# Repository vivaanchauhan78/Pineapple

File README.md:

# Pineapple
A not-so-small 60% keyboard that I made!

I have a mouse on my other setup up but I didn't have a keyboard, so I thought of making one!

| Item         | Cost    | Link |
|--------------|---------|------|
| Rpp2040      | $3.46   | [Buy on aliexpress](https://www.aliexpress.us/item/3256806217238860.html?spm=a2g0o.cart.0.0.2d6c38daTqjGkV&mp=1&pdp_npi=5%40dis%21USD%21USD%203.46%21USD%200.99%21%21USD%200.99%21%21%21%402103205217531554636108924eb90a%2112000037042067691%21ct%21US%216426456965%21%211%210&pdp_ext_f=%7B%22cart2PdpParams%22%3A%7B%22pdpBusinessMode%22%3A%22retail%22%7D%7D&_gl=1*w7bknt*_gcl_au*MTQ2NDQ1NzgyLjE3NTI4NzgwODk.*_ga*MTk1MzE5NzUxMi4xNzUzMDQ5NjA5*_ga_VED1YSGNC7*czE3NTMxNTQ2MDQkbzQkZzEkdDE3NTMxNTU0NjMkajMzJGwwJGgw&gatewayAdapt=glo2usa) |
| Switches     | $19.65  | [Buy on AliExpress](https://www.aliexpress.us/item/3256804049630074.html) |
| PCB          | $30.44  | [Buy on Pcbway](https://member.pcbway.com/Order/OrderGroupConfirm/)
| Stabilizers  | $4.11   | [Buy on aliexpress](https://www.aliexpress.us/item/3256807348740208.html?spm=a2g0o.productlist.main.4.7c5d4a6eayveZj&aem_p4p_detail=20250721204006133116881527110000082721&algo_pvid=e2a4ce2c-4b11-4272-be36-e702e015e351&algo_exp_id=e2a4ce2c-4b11-4272-be36-e702e015e351-3&pdp_ext_f=%7B%22order%22%3A%22365%22%2C%22eval%22%3A%221%22%7D&pdp_npi=4%40dis%21USD%214.11%210.99%21%21%2129.35%217.10%21%402103241117531556059128212efb0c%2112000041195815297%21sea%21US%216426456965%21ABX&curPageLogUid=ajEZrvKqLNbd&utparam-url=scene%3Asearch%7Cquery_from%3A&search_p4p_id=20250721204006133116881527110000082721_1) |
| Fasteners    | $14.00  | [Buy on eBay](https://pay.ebay.com/rgxo?action=view&sessionid=1716123654) |
| Diodes       | $1.64   | [Buy on AliExpress](https://www.aliexpress.us/p/trade/confirm.html?availableProductShopcartIds=81023549395923) |
| Keycaps      | $26.51  | [Buy on Amazon](https://www.amazon.com/JSJT-Keycaps-Keycaps-Non-Backlit-Mechanical-Multi-Color/dp/B0BCFCQG2Z/ref=asc_df_B0BCFCQG2Z?tag=bingshoppinga-20&linkCode=df0&hvadid=80333258220081&hvnetw=o&hvqmt=e&hvbmt=be&hvdev=c&hvlocint=&hvlocphy=77507&hvtargid=pla-4583932723308317&msclkid=375f23a88c8a1849a15e4bd658e5279e&th=1) |
| Case         | $4.74   |
| **Total**    | **104.55** | 

Pictures:

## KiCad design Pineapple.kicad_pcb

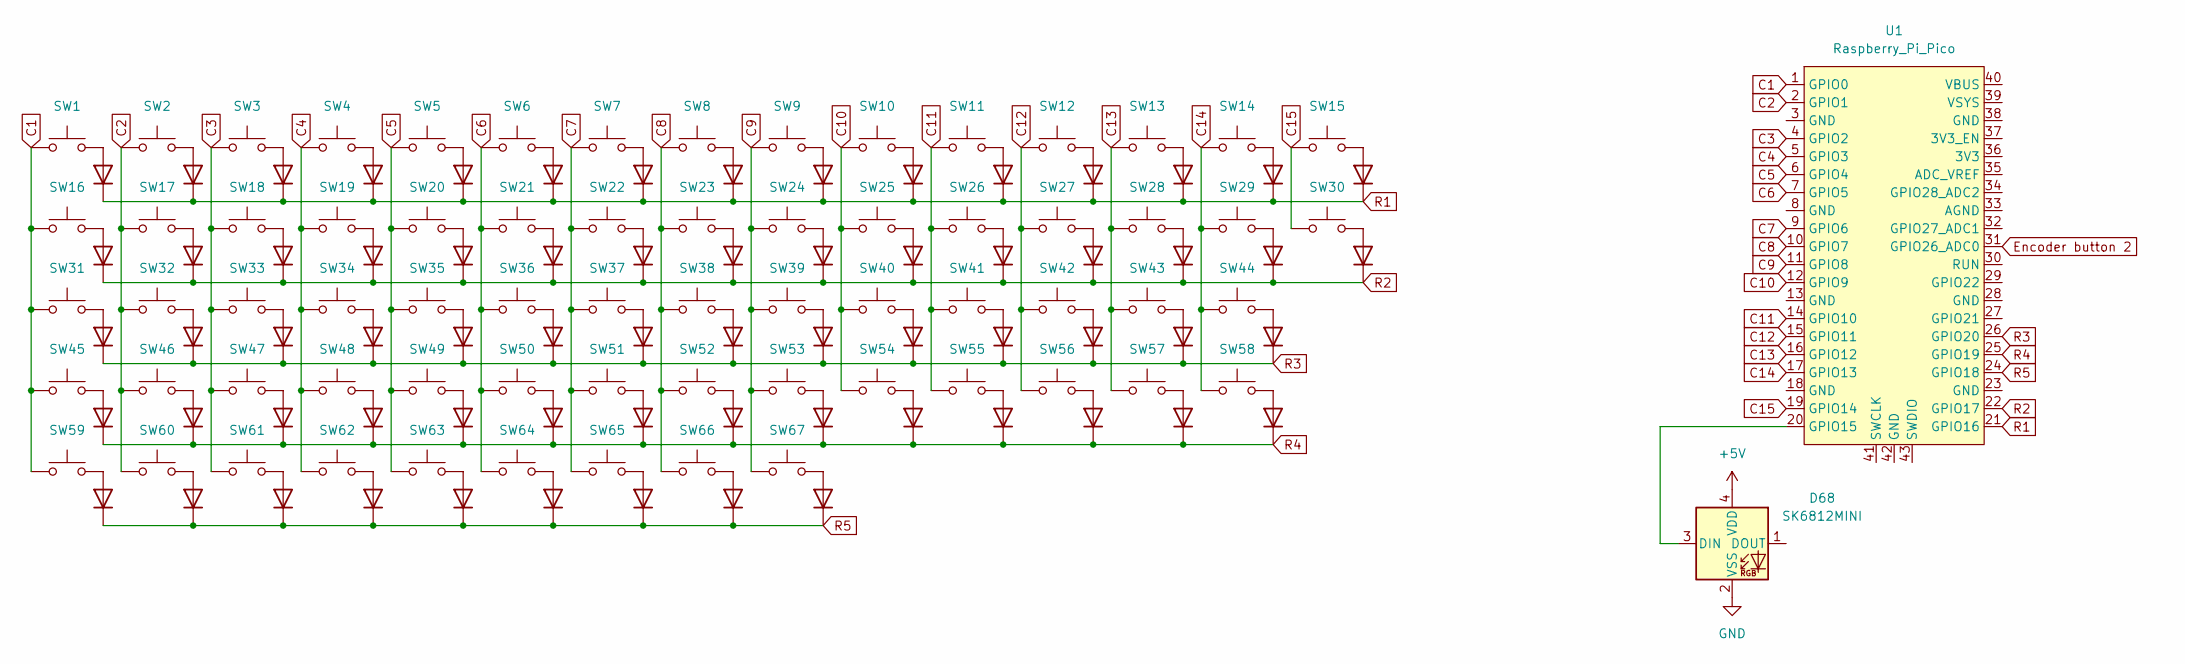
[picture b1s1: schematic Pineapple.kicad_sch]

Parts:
D1, D2, D3, D4, D5, D6, D7, D8, D9, D10, D11, D12, D13, D14, D15, D16, D17, D18, D19, D20, D21, D22, D23, D24, D25, D26, D27, D28, D29, D30, D31, D32, D33, D34, D35, D36, D37, D38, D39, D40, D41, D42, D43, D44, D45, D46, D47, D48, D49, D50, D51, D52, D53, D54, D55, D56, D57, D58, D59, D60, D61, D62, D63, D64, D65, D66, D67: D; D_DO-35_SOD27_P7.62mm_Horizontal
D68: SK6812MINI; LED_SK6812MINI_PLCC4_3.5x3.5mm_P1.75mm
SW1, SW2, SW3, SW4, SW5, SW6, SW7, SW8, SW9, SW10, SW11, SW12, SW13, SW15, SW17, SW18, SW19, SW20, SW21, SW22, SW23, SW24, SW25, SW26, SW27, SW28, SW30, SW32, SW33, SW34, SW35, SW36, SW37, SW38, SW39, SW40, SW41, SW42, SW44, SW46, SW47, SW48, SW49, SW50, SW51, SW52, SW53, SW54, SW55, SW57, SW58, SW65, SW66, SW67: SW_Push; SW_Cherry_MX_1.00u_PCB
SW14, SW31, SW56: SW_Push; SW_Cherry_MX_1.75u_PCB
SW16: SW_Push; SW_Cherry_MX_1.50u_PCB
SW29, SW59, SW60, SW61, SW63, SW64: SW_Push; SW_Cherry_MX_1.25u_PCB
SW43, SW45: SW_Push; SW_Cherry_MX_2.00u_PCB
SW62: SW_Push; SW_Cherry_MX_6.25u_PCB
U1: Raspberry_Pi_Pico

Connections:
+5V: D68.4 (VDD)
C1: SW1.1, SW16.1, SW31.1, SW45.1, SW59.1, U1.1 (GPIO0)
C2: SW2.1, SW17.1, SW32.1, SW46.1, SW60.1, U1.2 (GPIO1)
C3: SW3.2, SW18.1, SW33.1, SW47.1, SW61.1, U1.4 (GPIO2)
C4: SW4.1, SW19.1, SW34.1, SW48.1, SW62.1, U1.5 (GPIO3)
C5: SW5.1, SW20.1, SW35.1, SW49.1, SW63.1, U1.6 (GPIO4)
C6: SW6.1, SW21.1, SW36.1, SW50.1, SW64.1, U1.7 (GPIO5)
C7: SW7.1, SW22.1, SW37.1, SW51.1, SW65.1, U1.9 (GPIO6)
C8: SW8.1, SW23.1, SW38.1, SW52.1, SW66.1, U1.10 (GPIO7)
C9: SW9.1, SW24.1, SW39.1, SW53.1, SW67.1, U1.11 (GPIO8)
C10: SW10.1, SW25.1, SW40.1, SW54.1, U1.12 (GPIO9)
C11: SW11.1, SW26.1, SW41.1, SW55.1, U1.14 (GPIO10)
C12: SW12.1, SW27.1, SW42.1, SW56.1, U1.15 (GPIO11)
C13: SW13.1, SW28.1, SW43.1, SW57.1, U1.16 (GPIO12)
C14: SW14.1, SW29.1, SW44.1, SW58.1, U1.17 (GPIO13)
C15: SW15.1, SW30.1, U1.19 (GPIO14)
Encoder button 1: U1.29 (GPIO22)
Encoder button 2: U1.31 (GPIO26_ADC0)
GND: D68.2 (VSS)
unnamed: D1.2 (A), SW1.2
unnamed: D2.2 (A), SW2.2
unnamed: D3.2 (A), SW3.1
unnamed: D4.2 (A), SW4.2
unnamed: D5.2 (A), SW5.2
unnamed: D6.2 (A), SW6.2
unnamed: D7.2 (A), SW7.2
unnamed: D8.2 (A), SW8.2
unnamed: D9.2 (A), SW9.2
unnamed: D10.2 (A), SW10.2
unnamed: D11.2 (A), SW11.2
unnamed: D12.2 (A), SW12.2
unnamed: D13.2 (A), SW13.2
unnamed: D14.2 (A), SW14.2
unnamed: D15.2 (A), SW15.2
unnamed: D16.2 (A), SW16.2
unnamed: D17.2 (A), SW17.2
unnamed: D18.2 (A), SW18.2
unnamed: D19.2 (A), SW19.2
unnamed: D20.2 (A), SW20.2
unnamed: D21.2 (A), SW21.2
unnamed: D22.2 (A), SW22.2
unnamed: D23.2 (A), SW23.2
unnamed: D24.2 (A), SW24.2
unnamed: D25.2 (A), SW25.2
unnamed: D26.2 (A), SW26.2
unnamed: D27.2 (A), SW27.2
unnamed: D28.2 (A), SW28.2
unnamed: D29.2 (A), SW29.2
unnamed: D30.2 (A), SW30.2
unnamed: D31.2 (A), SW31.2
unnamed: D32.2 (A), SW32.2
unnamed: D33.2 (A), SW33.2
unnamed: D34.2 (A), SW34.2
unnamed: D35.2 (A), SW35.2
unnamed: D36.2 (A), SW36.2
unnamed: D37.2 (A), SW37.2
unnamed: D38.2 (A), SW38.2
unnamed: D39.2 (A), SW39.2
unnamed: D40.2 (A), SW40.2
unnamed: D41.2 (A), SW41.2
unnamed: D42.2 (A), SW42.2
unnamed: D43.2 (A), SW43.2
unnamed: D44.2 (A), SW44.2
unnamed: D45.2 (A), SW45.2
unnamed: D46.2 (A), SW46.2
unnamed: D47.2 (A), SW47.2
unnamed: D48.2 (A), SW48.2
unnamed: D49.2 (A), SW49.2
unnamed: D50.2 (A), SW50.2
unnamed: D51.2 (A), SW51.2
unnamed: D52.2 (A), SW52.2
unnamed: D53.2 (A), SW53.2
unnamed: D54.2 (A), SW54.2
unnamed: D55.2 (A), SW55.2
unnamed: D56.2 (A), SW56.2
unnamed: D57.2 (A), SW57.2
unnamed: D58.2 (A), SW58.2
unnamed: D59.2 (A), SW59.2
unnamed: D60.2 (A), SW60.2
unnamed: D61.2 (A), SW61.2
unnamed: D62.2 (A), SW62.2
unnamed: D63.2 (A), SW63.2
unnamed: D64.2 (A), SW64.2
unnamed: D65.2 (A), SW65.2
unnamed: D66.2 (A), SW66.2
unnamed: D67.2 (A), SW67.2
unnamed: D68.3 (DIN), U1.20 (GPIO15)
R1: D1.1 (K), D2.1 (K), D3.1 (K), D4.1 (K), D5.1 (K), D6.1 (K), D7.1 (K), D8.1 (K), D9.1 (K), D10.1 (K), D11.1 (K), D12.1 (K), D13.1 (K), D14.1 (K), D15.1 (K), U1.21 (GPIO16)
R2: D16.1 (K), D17.1 (K), D18.1 (K), D19.1 (K), D20.1 (K), D21.1 (K), D22.1 (K), D23.1 (K), D24.1 (K), D25.1 (K), D26.1 (K), D27.1 (K), D28.1 (K), D29.1 (K), D30.1 (K), U1.22 (GPIO17)
R3: D31.1 (K), D32.1 (K), D33.1 (K), D34.1 (K), D35.1 (K), D36.1 (K), D37.1 (K), D38.1 (K), D39.1 (K), D40.1 (K), D41.1 (K), D42.1 (K), D43.1 (K), D44.1 (K), U1.26 (GPIO20)
R4: D45.1 (K), D46.1 (K), D47.1 (K), D48.1 (K), D49.1 (K), D50.1 (K), D51.1 (K), D52.1 (K), D53.1 (K), D54.1 (K), D55.1 (K), D56.1 (K), D57.1 (K), D58.1 (K), U1.25 (GPIO19)
R5: D59.1 (K), D60.1 (K), D61.1 (K), D62.1 (K), D63.1 (K), D64.1 (K), D65.1 (K), D66.1 (K), D67.1 (K), U1.24 (GPIO18)

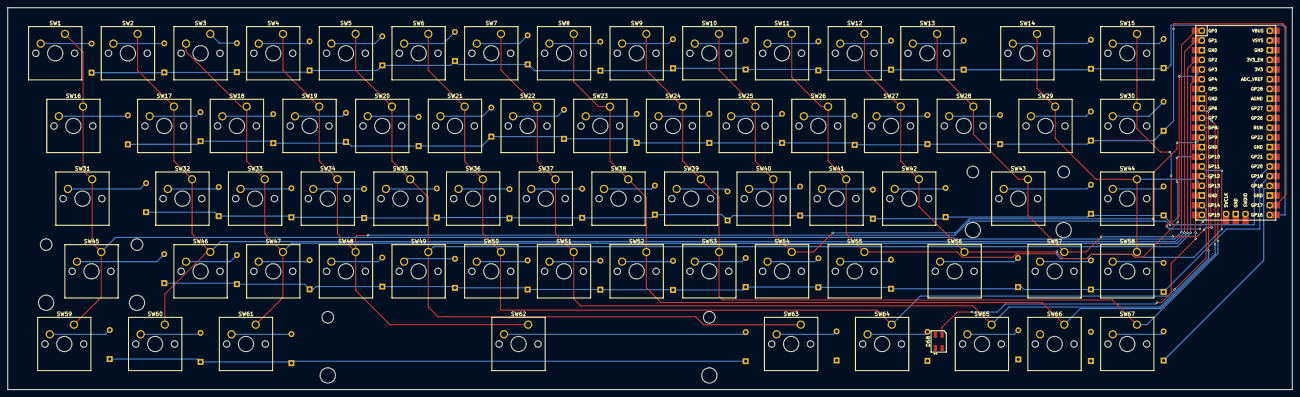
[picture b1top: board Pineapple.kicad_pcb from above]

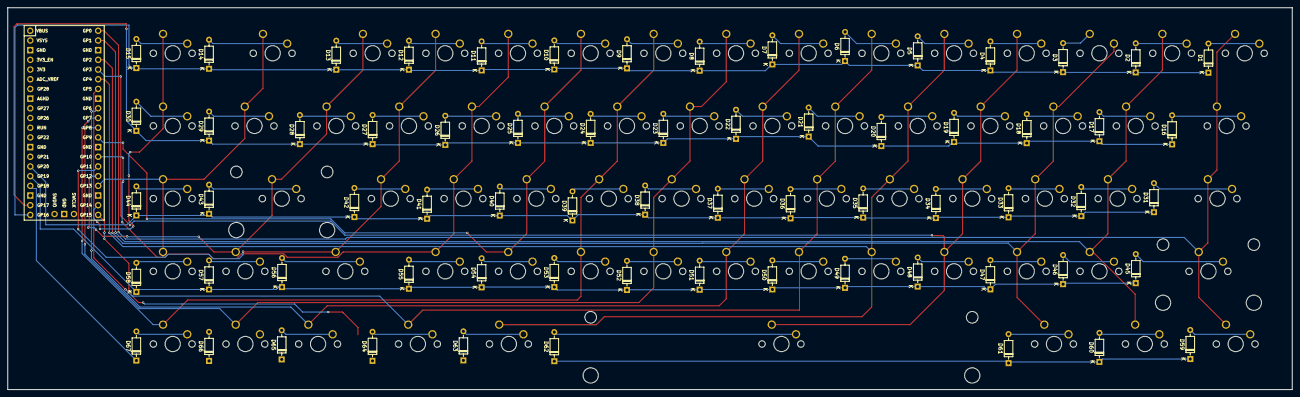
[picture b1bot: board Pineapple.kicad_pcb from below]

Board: 2 copper layers, 336.7 x 100.1 mm, 136 parts (67 on the bottom side), 88 nets.

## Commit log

2025-07-21 Create BOM
2025-08-02 Update bom
